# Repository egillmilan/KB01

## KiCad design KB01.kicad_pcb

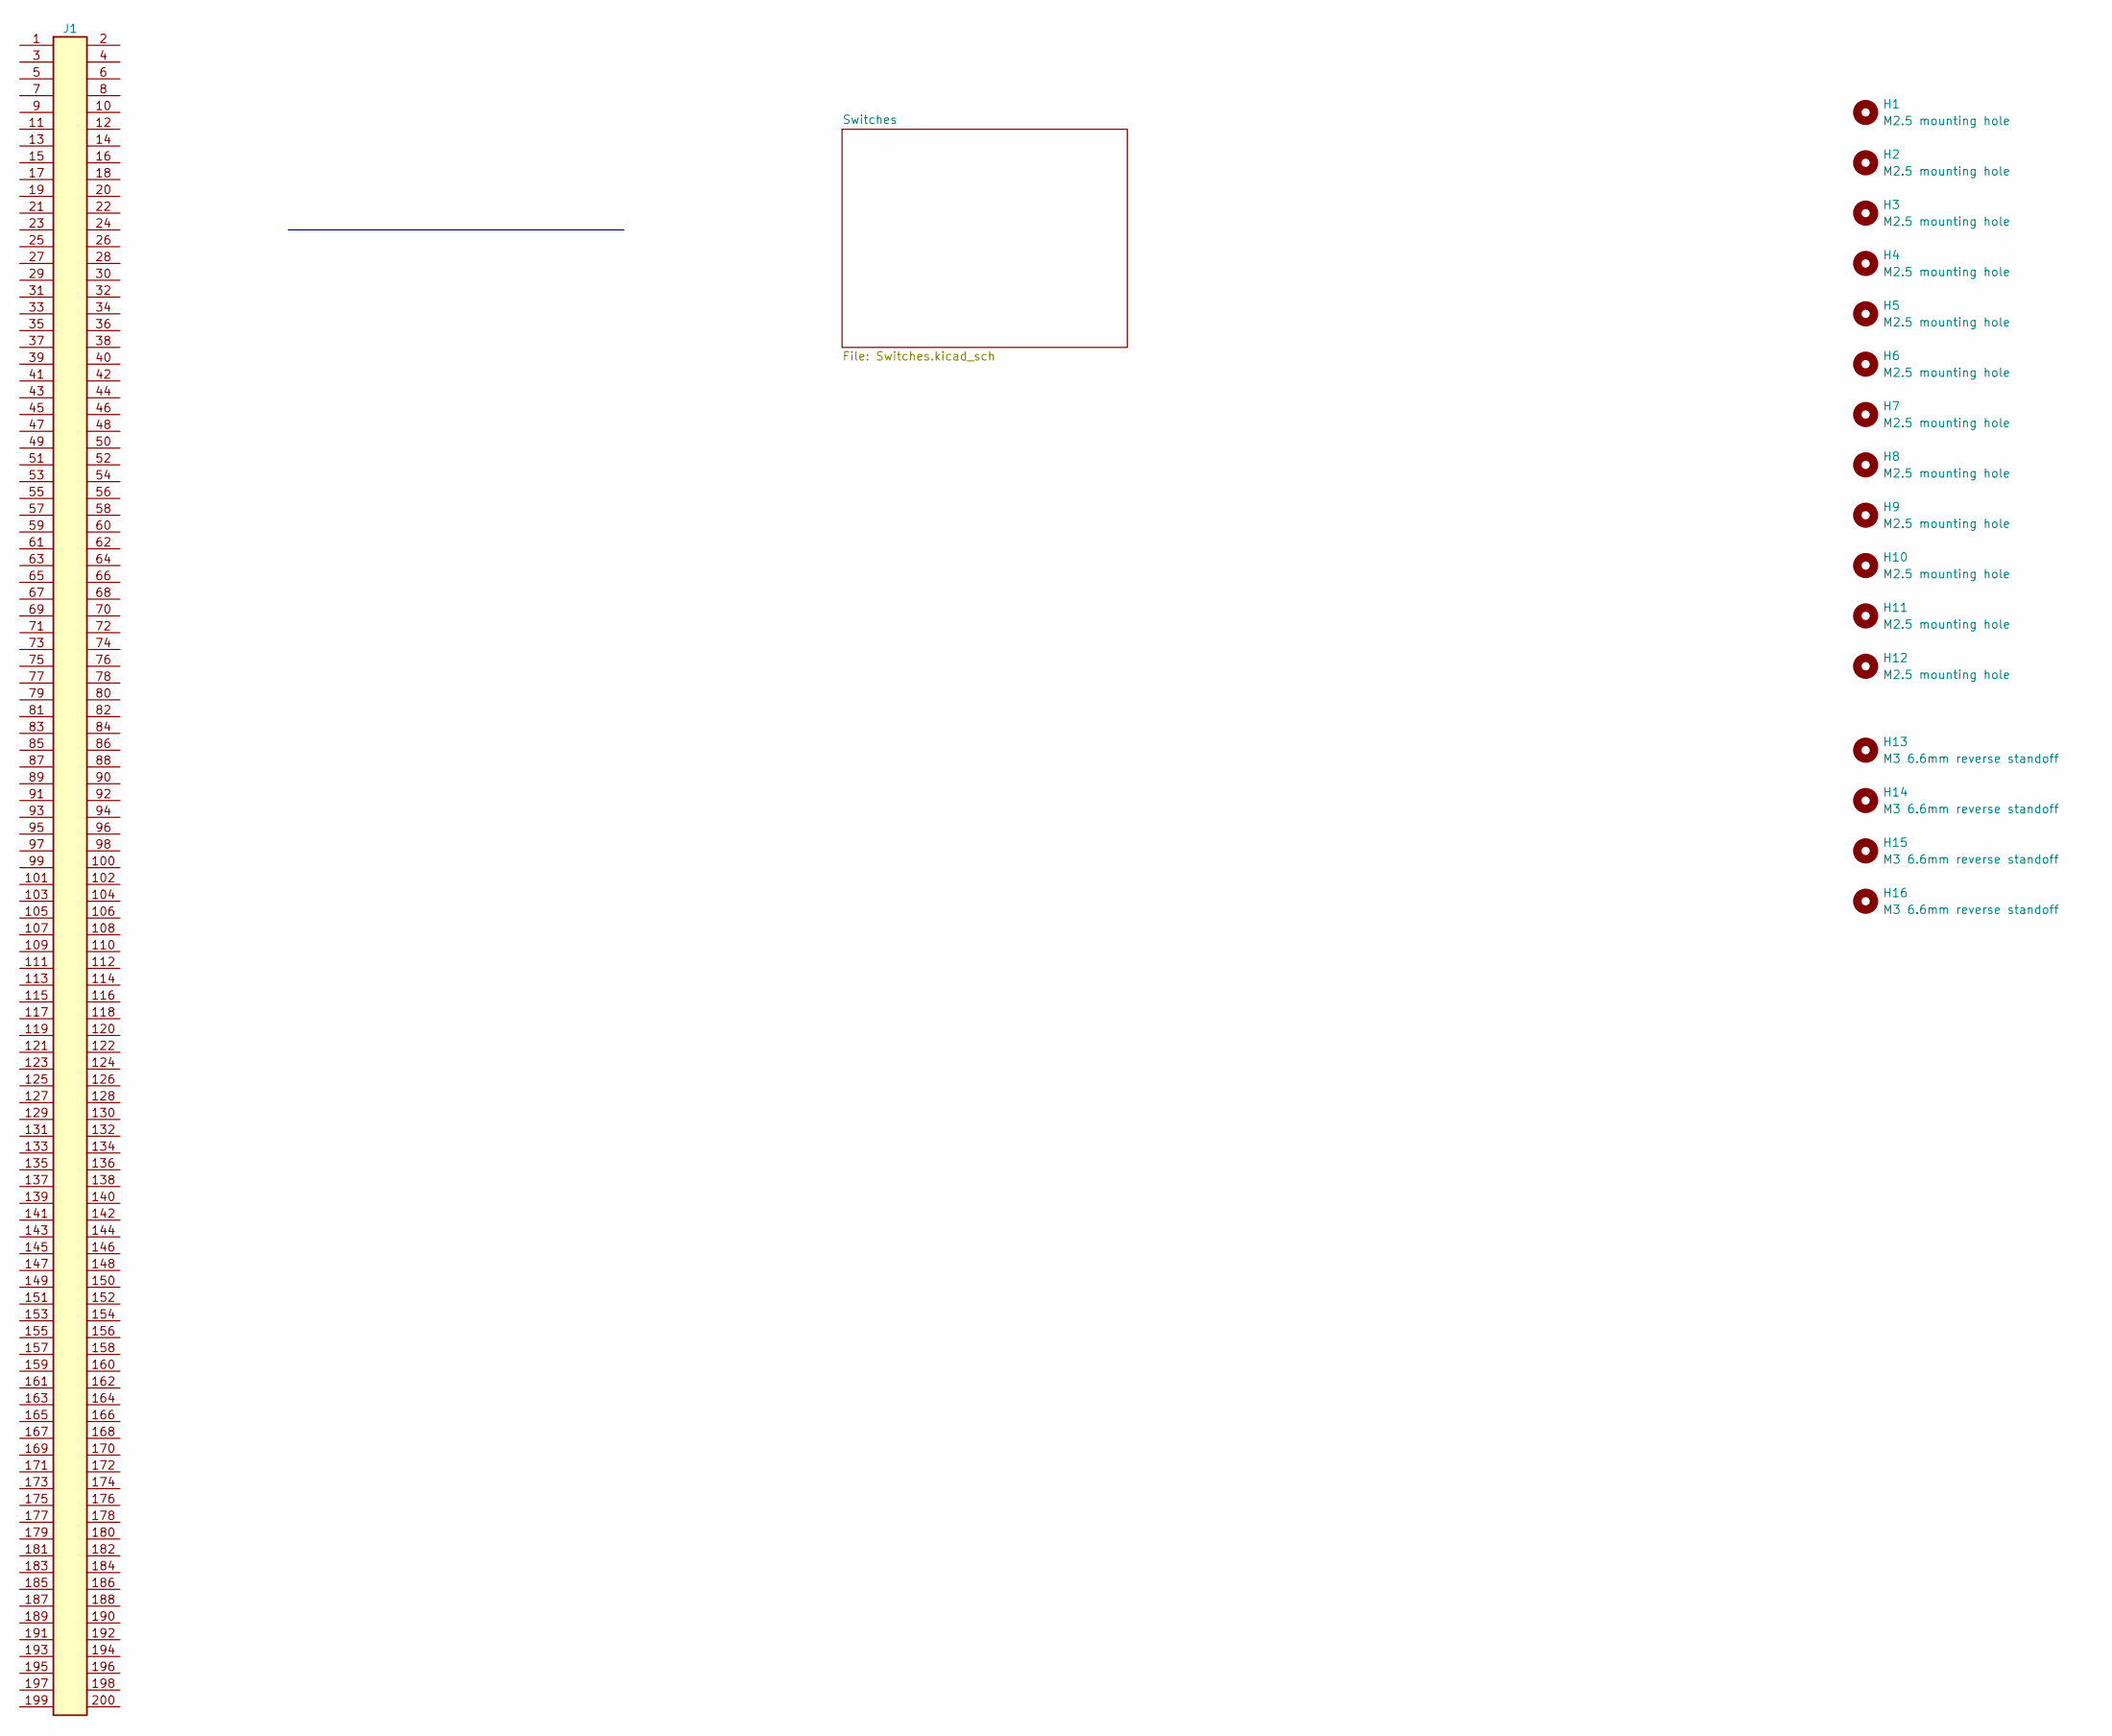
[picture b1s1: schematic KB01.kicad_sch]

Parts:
H1, H2, H3, H4, H5, H6, H7, H8, H9, H10, H11, H12: M2.5 mounting hole; MountingHole_2.7mm_M2.5
H13, H14, H15, H16: M3 6.6mm reverse standoff; Standoff_reverse-M3-6.6mm-SMD; Mfr. Part Number 9775066360R
J1: J-Samtec_BTS-Terminal-SMD-200p; Samtec_BTS-100-01-F-D-A; Mfr. Part Number BTS-100-01-F-D-A

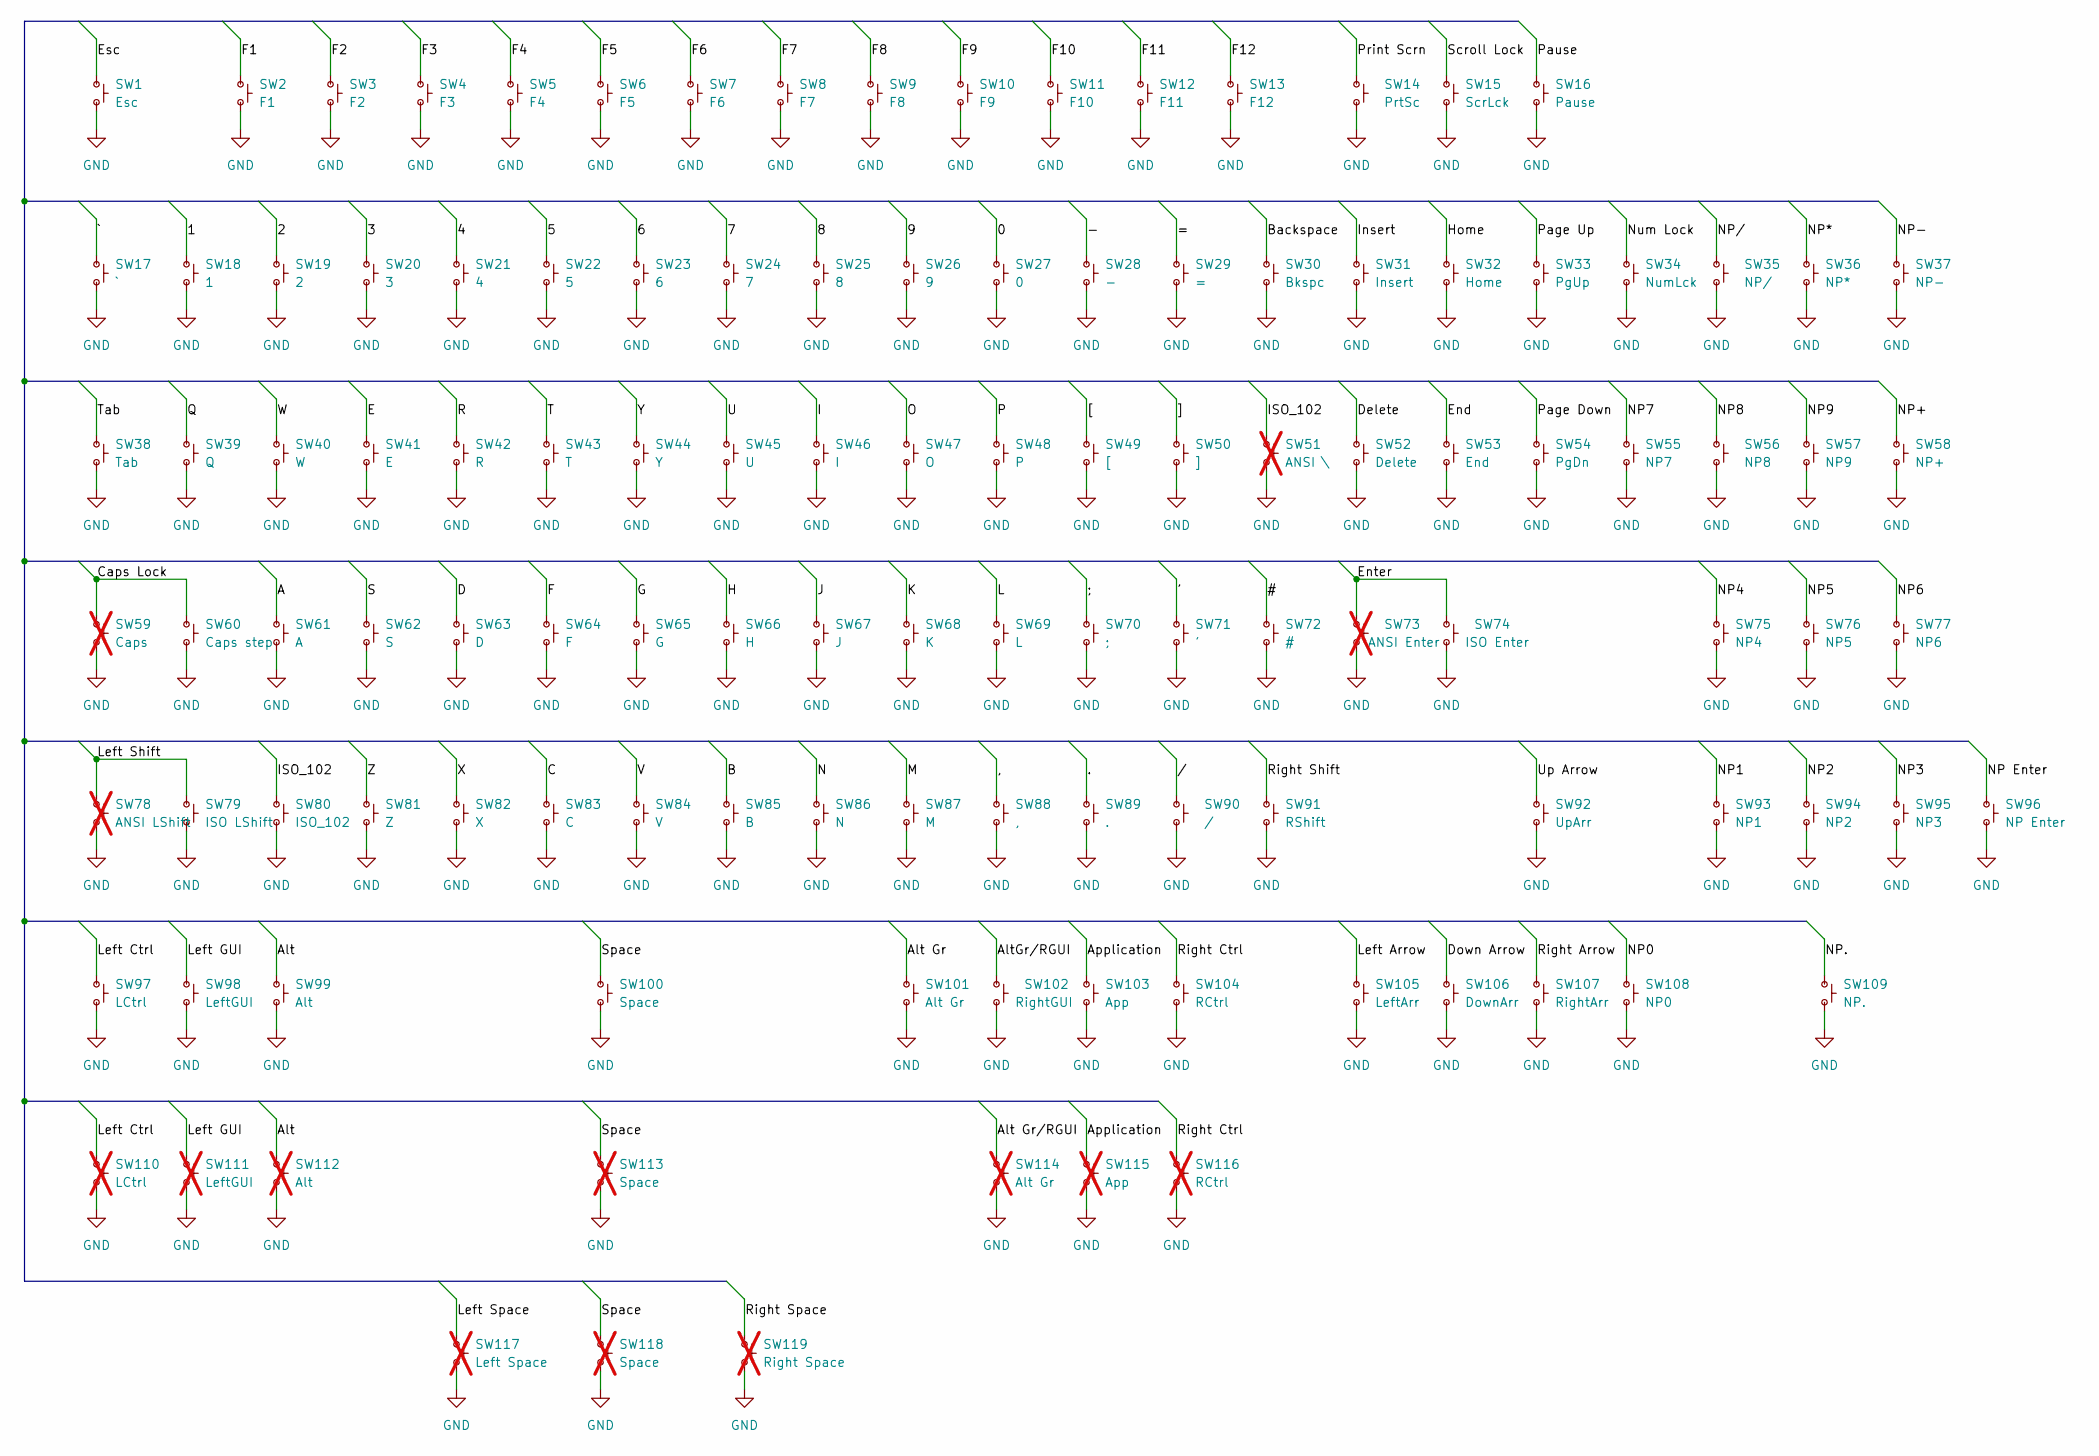
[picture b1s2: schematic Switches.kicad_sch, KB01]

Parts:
SW1: Esc; SW_Cherry_MX_R1_1.00u_PCB; Mfr. Part Number Chosen by user
SW2: F1; SW_Cherry_MX_R1_1.00u_PCB; Mfr. Part Number Chosen by user
SW3: F2; SW_Cherry_MX_R1_1.00u_PCB; Mfr. Part Number Chosen by user
SW4: F3; SW_Cherry_MX_R1_1.00u_PCB; Mfr. Part Number Chosen by user
SW5: F4; SW_Cherry_MX_R1_1.00u_PCB; Mfr. Part Number Chosen by user
SW6: F5; SW_Cherry_MX_R1_1.00u_PCB; Mfr. Part Number Chosen by user
SW7: F6; SW_Cherry_MX_R1_1.00u_PCB; Mfr. Part Number Chosen by user
SW8: F7; SW_Cherry_MX_R1_1.00u_PCB; Mfr. Part Number Chosen by user
SW9: F8; SW_Cherry_MX_R1_1.00u_PCB; Mfr. Part Number Chosen by user
SW10: F9; SW_Cherry_MX_R1_1.00u_PCB; Mfr. Part Number Chosen by user
SW11: F10; SW_Cherry_MX_R1_1.00u_PCB; Mfr. Part Number Chosen by user
SW12: F11; SW_Cherry_MX_R1_1.00u_PCB; Mfr. Part Number Chosen by user
SW13: F12; SW_Cherry_MX_R1_1.00u_PCB; Mfr. Part Number Chosen by user
SW14: PrtSc; SW_Cherry_MX_R1_1.00u_PCB; Mfr. Part Number Chosen by user
SW15: ScrLck; SW_Cherry_MX_R1_1.00u_PCB; Mfr. Part Number Chosen by user
SW16: Pause; SW_Cherry_MX_R1_1.00u_PCB; Mfr. Part Number Chosen by user
SW17: `; SW_Cherry_MX_R1_1.00u_PCB; Mfr. Part Number Chosen by user
SW18: 1; SW_Cherry_MX_R1_1.00u_PCB; Mfr. Part Number Chosen by user
SW19: 2; SW_Cherry_MX_R1_1.00u_PCB; Mfr. Part Number Chosen by user
SW20: 3; SW_Cherry_MX_R1_1.00u_PCB; Mfr. Part Number Chosen by user
SW21: 4; SW_Cherry_MX_R1_1.00u_PCB; Mfr. Part Number Chosen by user
SW22: 5; SW_Cherry_MX_R1_1.00u_PCB; Mfr. Part Number Chosen by user
SW23: 6; SW_Cherry_MX_R1_1.00u_PCB; Mfr. Part Number Chosen by user
SW24: 7; SW_Cherry_MX_R1_1.00u_PCB; Mfr. Part Number Chosen by user
SW25: 8; SW_Cherry_MX_R1_1.00u_PCB; Mfr. Part Number Chosen by user
SW26: 9; SW_Cherry_MX_R1_1.00u_PCB; Mfr. Part Number Chosen by user
SW27: 0; SW_Cherry_MX_R1_1.00u_PCB; Mfr. Part Number Chosen by user
SW28: -; SW_Cherry_MX_R1_1.00u_PCB; Mfr. Part Number Chosen by user
SW29: =; SW_Cherry_MX_R1_1.00u_PCB; Mfr. Part Number Chosen by user
SW30: Bkspc; SW_Cherry_MX_R1_2.00u_PCB; Mfr. Part Number Chosen by user
SW31: Insert; SW_Cherry_MX_R1_1.00u_PCB; Mfr. Part Number Chosen by user
SW32: Home; SW_Cherry_MX_R1_1.00u_PCB; Mfr. Part Number Chosen by user
SW33: PgUp; SW_Cherry_MX_R1_1.00u_PCB; Mfr. Part Number Chosen by user
SW34: NumLck; SW_Cherry_MX_R1_1.00u_PCB; Mfr. Part Number Chosen by user
SW35: NP/; SW_Cherry_MX_R1_1.00u_PCB; Mfr. Part Number Chosen by user
SW36: NP*; SW_Cherry_MX_R1_1.00u_PCB; Mfr. Part Number Chosen by user
SW37: NP-; SW_Cherry_MX_R1_1.00u_PCB; Mfr. Part Number Chosen by user
SW38: Tab; SW_Cherry_MX_R2_1.50u_PCB; Mfr. Part Number Chosen by user
SW39: Q; SW_Cherry_MX_R2_1.00u_PCB; Mfr. Part Number Chosen by user
SW40: W; SW_Cherry_MX_R2_1.00u_PCB; Mfr. Part Number Chosen by user
SW41: E; SW_Cherry_MX_R2_1.00u_PCB; Mfr. Part Number Chosen by user
SW42: R; SW_Cherry_MX_R2_1.00u_PCB; Mfr. Part Number Chosen by user
SW43: T; SW_Cherry_MX_R2_1.00u_PCB; Mfr. Part Number Chosen by user
SW44: Y; SW_Cherry_MX_R2_1.00u_PCB; Mfr. Part Number Chosen by user
SW45: U; SW_Cherry_MX_R2_1.00u_PCB; Mfr. Part Number Chosen by user
SW46: I; SW_Cherry_MX_R2_1.00u_PCB; Mfr. Part Number Chosen by user
SW47: O; SW_Cherry_MX_R2_1.00u_PCB; Mfr. Part Number Chosen by user
SW48: P; SW_Cherry_MX_R2_1.00u_PCB; Mfr. Part Number Chosen by user
SW49: [; SW_Cherry_MX_R2_1.00u_PCB; Mfr. Part Number Chosen by user
SW50: ]; SW_Cherry_MX_R2_1.00u_PCB; Mfr. Part Number Chosen by user
SW51: ANSI \; SW_Cherry_MX_R2_1.50u_PCB; Mfr. Part Number Chosen by user; not fitted
SW52: Delete; SW_Cherry_MX_R2_1.00u_PCB; Mfr. Part Number Chosen by user
SW53: End; SW_Cherry_MX_R2_1.00u_PCB; Mfr. Part Number Chosen by user
SW54: PgDn; SW_Cherry_MX_R2_1.00u_PCB; Mfr. Part Number Chosen by user
SW55: NP7; SW_Cherry_MX_R2_1.00u_PCB; Mfr. Part Number Chosen by user
SW56: NP8; SW_Cherry_MX_R2_1.00u_PCB; Mfr. Part Number Chosen by user
SW57: NP9; SW_Cherry_MX_R2_1.00u_PCB; Mfr. Part Number Chosen by user
SW58: NP+; SW_Cherry_MX_R2-R3_1.00u_PCB; Mfr. Part Number Chosen by user
SW59: Caps; SW_Cherry_MX_R3_1.75u_Stepped_PCB; Mfr. Part Number Chosen by user; not fitted
SW60: Caps step; SW_Cherry_MX_R3_1.75u_PCB; Mfr. Part Number Chosen by user
SW61: A; SW_Cherry_MX_R3_1.00u_PCB; Mfr. Part Number Chosen by user
SW62: S; SW_Cherry_MX_R3_1.00u_PCB; Mfr. Part Number Chosen by user
SW63: D; SW_Cherry_MX_R3_1.00u_PCB; Mfr. Part Number Chosen by user
SW64: F; SW_Cherry_MX_R3_1.00u_PCB; Mfr. Part Number Chosen by user
SW65: G; SW_Cherry_MX_R3_1.00u_PCB; Mfr. Part Number Chosen by user
SW66: H; SW_Cherry_MX_R3_1.00u_PCB; Mfr. Part Number Chosen by user
SW67: J; SW_Cherry_MX_R3_1.00u_PCB; Mfr. Part Number Chosen by user
SW68: K; SW_Cherry_MX_R3_1.00u_PCB; Mfr. Part Number Chosen by user
SW69: L; SW_Cherry_MX_R3_1.00u_PCB; Mfr. Part Number Chosen by user
SW70: ;; SW_Cherry_MX_R3_1.00u_PCB; Mfr. Part Number Chosen by user
SW71: '; SW_Cherry_MX_R3_1.00u_PCB; Mfr. Part Number Chosen by user
SW72: #; SW_Cherry_MX_R3_1.00u_PCB; Mfr. Part Number Chosen by user
SW73: ANSI Enter; SW_Cherry_MX_R3_2.25u_PCB; Mfr. Part Number Chosen by user; not fitted
SW74: ISO Enter; SW_Cherry_MX_ISO_Enter_PCB; Mfr. Part Number Chosen by user
SW75: NP4; SW_Cherry_MX_R3_1.00u_PCB; Mfr. Part Number Chosen by user
SW76: NP5; SW_Cherry_MX_R3_1.00u_PCB; Mfr. Part Number Chosen by user
SW77: NP6; SW_Cherry_MX_R3_1.00u_PCB; Mfr. Part Number Chosen by user
SW78: ANSI LShift; SW_Cherry_MX_R4_2.25u_PCB; Mfr. Part Number Chosen by user; not fitted
SW79: ISO LShift; SW_Cherry_MX_R4_1.25u_PCB; Mfr. Part Number Chosen by user
SW80: ISO_102; SW_Cherry_MX_R4_1.00u_PCB; Mfr. Part Number Chosen by user
SW81: Z; SW_Cherry_MX_R4_1.00u_PCB; Mfr. Part Number Chosen by user
SW82: X; SW_Cherry_MX_R4_1.00u_PCB; Mfr. Part Number Chosen by user
SW83: C; SW_Cherry_MX_R4_1.00u_PCB; Mfr. Part Number Chosen by user
SW84: V; SW_Cherry_MX_R4_1.00u_PCB; Mfr. Part Number Chosen by user
SW85: B; SW_Cherry_MX_R4_1.00u_PCB; Mfr. Part Number Chosen by user
SW86: N; SW_Cherry_MX_R4_1.00u_PCB; Mfr. Part Number Chosen by user
SW87: M; SW_Cherry_MX_R4_1.00u_PCB; Mfr. Part Number Chosen by user
SW88: ,; SW_Cherry_MX_R4_1.00u_PCB; Mfr. Part Number Chosen by user
SW89: .; SW_Cherry_MX_R4_1.00u_PCB; Mfr. Part Number Chosen by user
SW90: /; SW_Cherry_MX_R4_1.00u_PCB; Mfr. Part Number Chosen by user
SW91: RShift; SW_Cherry_MX_R4_2.75u_PCB; Mfr. Part Number Chosen by user
SW92: UpArr; SW_Cherry_MX_R4_1.00u_PCB; Mfr. Part Number Chosen by user
SW93: NP1; SW_Cherry_MX_R4_1.00u_PCB; Mfr. Part Number Chosen by user
SW94: NP2; SW_Cherry_MX_R4_1.00u_PCB; Mfr. Part Number Chosen by user
SW95: NP3; SW_Cherry_MX_R4_1.00u_PCB; Mfr. Part Number Chosen by user
SW96: NP Enter; SW_Cherry_MX_R4-R4_1.00u_PCB; Mfr. Part Number Chosen by user
SW97: LCtrl; SW_Cherry_MX_R4_1.25u_PCB; Mfr. Part Number Chosen by user
SW98: LeftGUI; SW_Cherry_MX_R4_1.25u_PCB; Mfr. Part Number Chosen by user
SW99: Alt; SW_Cherry_MX_R4_1.25u_PCB; Mfr. Part Number Chosen by user
SW100: Space; SW_Cherry_MX_Convex_6.25u_PCB; Mfr. Part Number Chosen by user
SW101: Alt Gr; SW_Cherry_MX_R4_1.25u_PCB; Mfr. Part Number Chosen by user
SW102: RightGUI; SW_Cherry_MX_R4_1.25u_PCB; Mfr. Part Number Chosen by user
SW103: App; SW_Cherry_MX_R4_1.25u_PCB; Mfr. Part Number Chosen by user
SW104: RCtrl; SW_Cherry_MX_R4_1.25u_PCB; Mfr. Part Number Chosen by user
SW105: LeftArr; SW_Cherry_MX_R4_1.00u_PCB; Mfr. Part Number Chosen by user
SW106: DownArr; SW_Cherry_MX_R4_1.00u_PCB; Mfr. Part Number Chosen by user
SW107: RightArr; SW_Cherry_MX_R4_1.00u_PCB; Mfr. Part Number Chosen by user
SW108: NP0; SW_Cherry_MX_R4_2.00u_PCB; Mfr. Part Number Chosen by user
SW109: NP.; SW_Cherry_MX_R4_1.00u_PCB; Mfr. Part Number Chosen by user
SW110: LCtrl; SW_Cherry_MX_R4_1.50u_PCB; Mfr. Part Number Chosen by user; not fitted
SW111: LeftGUI; SW_Cherry_MX_R4_1.00u_PCB; Mfr. Part Number Chosen by user; not fitted
SW112: Alt; SW_Cherry_MX_R4_1.50u_PCB; Mfr. Part Number Chosen by user; not fitted
SW113: Space; SW_Cherry_MX_Convex_7.00u_PCB; Mfr. Part Number Chosen by user; not fitted
SW114: Alt Gr; SW_Cherry_MX_R4_1.50u_PCB; Mfr. Part Number Chosen by user; not fitted
SW115: App; SW_Cherry_MX_R4_1.00u_PCB; Mfr. Part Number Chosen by user; not fitted
SW116: RCtrl; SW_Cherry_MX_R4_1.50u_PCB; Mfr. Part Number Chosen by user; not fitted
SW117: Left Space; SW_Cherry_MX_Convex_2.75u_PCB; Mfr. Part Number Chosen by user; not fitted
SW118: Space; SW_Cherry_MX_Convex_1.00u_PCB; Mfr. Part Number Chosen by user; not fitted
SW119: Right Space; SW_Cherry_MX_Convex_2.25u_PCB; Mfr. Part Number Chosen by user; not fitted

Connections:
/Switches/0: SW27.1
/Switches/1: SW18.1
/Switches/2: SW19.1
/Switches/3: SW20.1
/Switches/4: SW21.1
/Switches/5: SW22.1
/Switches/6: SW23.1
/Switches/7: SW24.1
/Switches/8: SW25.1
/Switches/9: SW26.1
/Switches/#: SW72.1
/Switches/': SW71.1
/Switches/,: SW88.1
/Switches/-: SW28.1
/Switches/.: SW89.1
/Switches/;: SW70.1
/Switches/=: SW29.1
/Switches/A: SW61.1
/Switches/Alt: SW99.1, SW112.1
/Switches/Alt Gr: SW101.1
/Switches/Alt Gr/RGUI: SW114.1
/Switches/AltGr/RGUI: SW102.1
/Switches/Application: SW103.1, SW115.1
/Switches/B: SW85.1
/Switches/Backspace: SW30.1
/Switches/C: SW83.1
/Switches/Caps Lock: SW59.1, SW60.1
/Switches/D: SW63.1
/Switches/Delete: SW52.1
/Switches/Down Arrow: SW106.1
/Switches/E: SW41.1
/Switches/End: SW53.1
/Switches/Enter: SW73.1, SW74.1
/Switches/Esc: SW1.1
/Switches/F: SW64.1
/Switches/F1: SW2.1
/Switches/F2: SW3.1
/Switches/F3: SW4.1
/Switches/F4: SW5.1
/Switches/F5: SW6.1
/Switches/F6: SW7.1
/Switches/F7: SW8.1
/Switches/F8: SW9.1
/Switches/F9: SW10.1
/Switches/F10: SW11.1
/Switches/F11: SW12.1
/Switches/F12: SW13.1
/Switches/G: SW65.1
/Switches/H: SW66.1
/Switches/Home: SW32.1
/Switches/I: SW46.1
/Switches/ISO_102: SW51.1, SW80.1
/Switches/Insert: SW31.1
/Switches/J: SW67.1
/Switches/K: SW68.1
/Switches/L: SW69.1
/Switches/Left Arrow: SW105.1
/Switches/Left Ctrl: SW97.1, SW110.1
/Switches/Left GUI: SW98.1, SW111.1
/Switches/Left Shift: SW78.1, SW79.1
/Switches/Left Space: SW117.1
/Switches/M: SW87.1
/Switches/N: SW86.1
/Switches/NP0: SW108.1
/Switches/NP1: SW93.1
/Switches/NP2: SW94.1
/Switches/NP3: SW95.1
/Switches/NP4: SW75.1
/Switches/NP5: SW76.1
/Switches/NP6: SW77.1
/Switches/NP7: SW55.1
/Switches/NP8: SW56.1
/Switches/NP9: SW57.1
/Switches/NP Enter: SW96.1
/Switches/NP*: SW36.1
/Switches/NP+: SW58.1
/Switches/NP-: SW37.1
/Switches/NP.: SW109.1
/Switches/NP/: SW35.1
/Switches/Num Lock: SW34.1
/Switches/O: SW47.1
/Switches/P: SW48.1
/Switches/Page Down: SW54.1
/Switches/Page Up: SW33.1
/Switches/Pause: SW16.1
/Switches/Print Scrn: SW14.1
/Switches/Q: SW39.1
/Switches/R: SW42.1
/Switches/Right Arrow: SW107.1
/Switches/Right Ctrl: SW104.1, SW116.1
/Switches/Right Shift: SW91.1
/Switches/Right Space: SW119.1
/Switches/S: SW62.1
/Switches/Scroll Lock: SW15.1
/Switches/Space: SW100.1, SW113.1, SW118.1
/Switches/T: SW43.1
/Switches/Tab: SW38.1
/Switches/U: SW45.1
/Switches/Up Arrow: SW92.1
/Switches/V: SW84.1
/Switches/W: SW40.1
/Switches/X: SW82.1
/Switches/Y: SW44.1
/Switches/Z: SW81.1
/Switches/[: SW49.1
/Switches/]: SW50.1
/Switches/`: SW17.1
/Switches//: SW90.1
GND: SW1.2, SW2.2, SW3.2, SW4.2, SW5.2, SW6.2, SW7.2, SW8.2, SW9.2, SW10.2, SW11.2, SW12.2, SW13.2, SW14.2, SW15.2, SW16.2, SW17.2, SW18.2, SW19.2, SW20.2, SW21.2, SW22.2, SW23.2, SW24.2, SW25.2, SW26.2, SW27.2, SW28.2, SW29.2, SW30.2, SW31.2, SW32.2, SW33.2, SW34.2, SW35.2, SW36.2, SW37.2, SW38.2, SW39.2, SW40.2, SW41.2, SW42.2, SW43.2, SW44.2, SW45.2, SW46.2, SW47.2, SW48.2, SW49.2, SW50.2, SW51.2, SW52.2, SW53.2, SW54.2, SW55.2, SW56.2, SW57.2, SW58.2, SW59.2, SW60.2, SW61.2, SW62.2, SW63.2, SW64.2, SW65.2, SW66.2, SW67.2, SW68.2, SW69.2, SW70.2, SW71.2, SW72.2, SW73.2, SW74.2, SW75.2, SW76.2, SW77.2, SW78.2, SW79.2, SW80.2, SW81.2, SW82.2, SW83.2, SW84.2, SW85.2, SW86.2, SW87.2, SW88.2, SW89.2, SW90.2, SW91.2, SW92.2, SW93.2, SW94.2, SW95.2, SW96.2, SW97.2, SW98.2, SW99.2, SW100.2, SW101.2, SW102.2, SW103.2, SW104.2, SW105.2, SW106.2, SW107.2, SW108.2, SW109.2, SW110.2, SW111.2, SW112.2, SW113.2, SW114.2, SW115.2, SW116.2, SW117.2, SW118.2, SW119.2

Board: 2 copper layers, 136 parts (1 on the bottom side), 11 nets, no tracks yet.

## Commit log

2025-12-23 added switches sheet and gitignore
2025-12-29 updates to board-to-board connector placement
2026-01-04 Update KB01.kicad_pcb
    minor edits
